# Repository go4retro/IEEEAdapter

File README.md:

# IEEE Adapter
PET/CBM IEEE edge connector to Centronics 24 adapter

## Introduction

Most likely (though I cannot confirm) the cost of placing a Centronics 24 connector on the PET 2001 motherboard and the unknown adoption of IEEE devices led Commodore to skip the connector and simply bring all signals needed to a .156" 12/24 pin male edge connector on the back of the unit.  Since the peripherals included the proper connector, Commodore then sold a special cable that contained the proper connector on one end and an female edge connector on the other end. PET/CBM owners would then need 1 of these cables at the start of the IEEE chain. Since reproducing this cable is cost prohibitive, this device economically converts from the .156" 12/24 connector the the Centronics-24 connector. The device is strictly passive, though the IFC signals can be switched or jumpered if desired.

## Purchase

The finished unit is available for purchase from [RETRO Innovations](http://store.go4retro.com/ieee-cable-adapter/).

## License

Copyright (C) 2012-20  RETRO Innovations

These files are free designs; you can redistribute them and/or modify
them under the terms of the Creative Commons Attribution-ShareAlike 
4.0 International License.

You should have received a copy of the license along with this
work. If not, see <http://creativecommons.org/licenses/by-sa/4.0/>.

These files are distributed in the hope that they will be useful,
but WITHOUT ANY WARRANTY; without even the implied warranty of
MERCHANTABILITY or FITNESS FOR A PARTICULAR PURPOSE.  See the
license for more details.

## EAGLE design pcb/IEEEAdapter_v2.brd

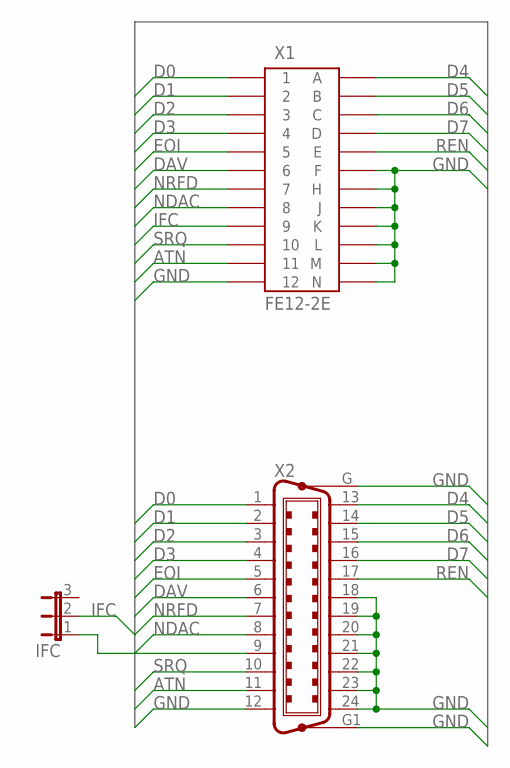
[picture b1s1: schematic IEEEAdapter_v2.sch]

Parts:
IFC: JP2E; JP2
X1: FE12-2E; FE12-2_SHORT
X2: C24HP; 24HP

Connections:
ATN: X1.11, X2.11
D0: X1.1, X2.1
D1: X1.2, X2.2
D2: X1.3, X2.3
D3: X1.4, X2.4
D4: X1.A, X2.13
D5: X1.B, X2.14
D6: X1.C, X2.15
D7: X1.D, X2.16
DAV: X1.6, X2.6
EOI: X1.5, X2.5
GND: X1.12, X1.F, X1.H, X1.J, X1.K, X1.L, X1.M, X1.N, X2.12, X2.18, X2.19, X2.20, X2.21, X2.22, X2.23, X2.24, X2.G, X2.G1
IFC: IFC.2, X1.9
unnamed: IFC.1, X2.9
NDAC: X1.8, X2.8
NRFD: X1.7, X2.7
REN: X1.E, X2.17
SRQ: X1.10, X2.10

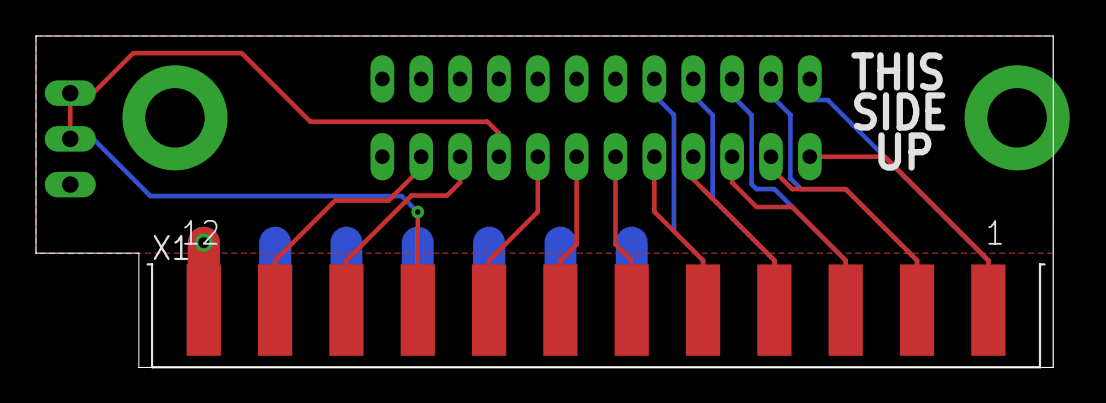
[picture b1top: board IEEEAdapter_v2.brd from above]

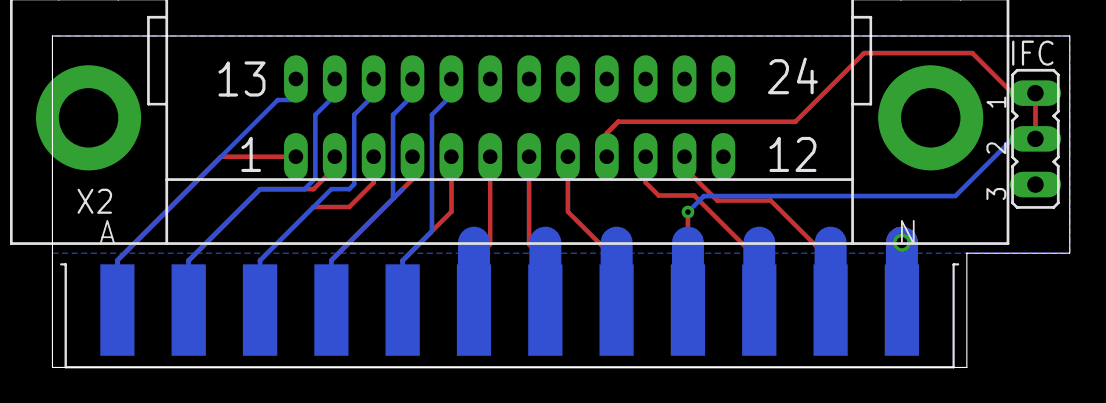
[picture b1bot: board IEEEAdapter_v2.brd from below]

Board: 2 copper layers, 56.5 x 18.4 mm, 3 parts (2 on the bottom side), 18 nets.

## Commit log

2020-10-18 Add purchase link
